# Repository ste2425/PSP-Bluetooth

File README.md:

# PSP-Bluetooth

--- 

ℹ️ **Name Change**  This project was formerly called the `PSP-Consolizer`. The project has since been renamed to `PSP-Bluetooth` as the term `Consolizer` usually makes people think of video output which this project never worked with. 

If you wish to see the legacy `PSP-Consolizer` project it is accessible on the `legacy` branch [here](https://github.com/ste2425/PSP-Bluetooth/tree/legacy)

---

This project aims to add Bluetooth controller support to the PSP 1k, 2k and 3k models using an ESP32.

---

It aims to solve to problems:

- [x] Using the PSP as a consolizer
- [ ] Using the PSP as a dockable console (like the Nintendo Switch)

## Progress so far
* Fully functional hardware that replaces the UMD drive
* Partially functional hardware for portable version
* Fully functional consolizer implementation that works for both the 2K and 3K consoles
* Fully functional firmware that offer configurable controller mappings and OTA updates
* Single click programming via a Web app for Serial and OTA programming. No extra tools needed, it downloads the binaries and does everything
* Partially functional controller mappings via the web app.

## Web app

The web app can be found here [PSP-Bluetooth](https://ste2425.github.io/PSP-Bluetooth/).

## Repository Structure

### /software

This contains the firmware for the ESP32. It is built using the Arduino core and maanaged via the Arduino CLI. To build it the cli needs to be installed with the command `arduino-cli` globally available. 

See [it's readme](./software/Readme.md) for more info.

### /installer

This contains the software for the Web app. It as an Angular application built using Angular Material and deployed to GitHub pages via GitHub Actions.

See [it's readme](./installer/README.md) for more info.

### /Hardware

This contians all the hardware files for custom FPC's and the mod board itself.

See [it's readme](./hardware/Readme.md) for more info.

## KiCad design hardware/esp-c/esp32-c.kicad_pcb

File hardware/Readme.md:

# Hardware

This is the source for the Kicad project for the PSP Bluetooth hardware.

# Parts

I use JLCPCB for my assembly and as such the parts used are sourced from their catalog.

## Adding a part

See [Changing Parts](./ChangingParts.md) for more info.

## Generating JLCPCB production files

See [Generating Gerbers](./GenerateGerbers.md) for more info.

# Projects

# Analog

FPC for the analog stick intercept for 2K PSP's. This allows us to inject analog stick values without soldering to the console.

# Buttons Super

FPC for all the buttons intercepts for 2k PSP's combined into a single project. Fabs usually charge extra for all being combined into one.

# Center Buttons

FPC for the center buttons intercept for 2K PSP'script

# ESP

Project for the Mod Board which supports both portable and consolizer

# ESP-C

Project for the Mod Board which only support consolizers. The analog multiplexer for the analog sticks are missing here.

# Right

FPC for just the right buttons for 2K PSP's

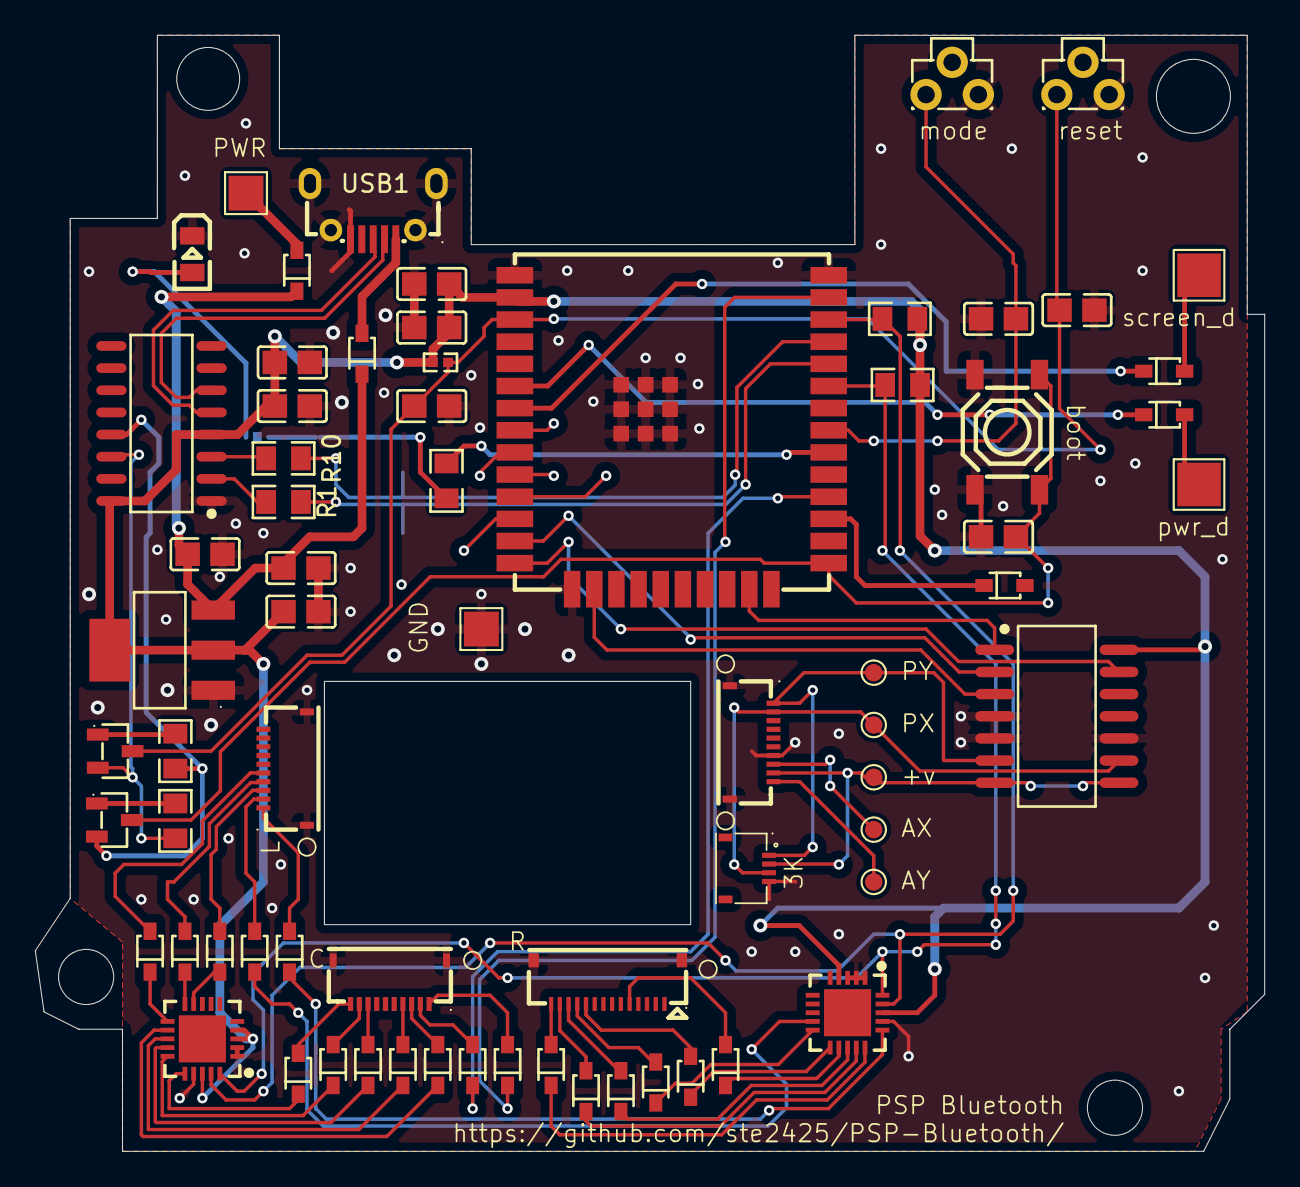
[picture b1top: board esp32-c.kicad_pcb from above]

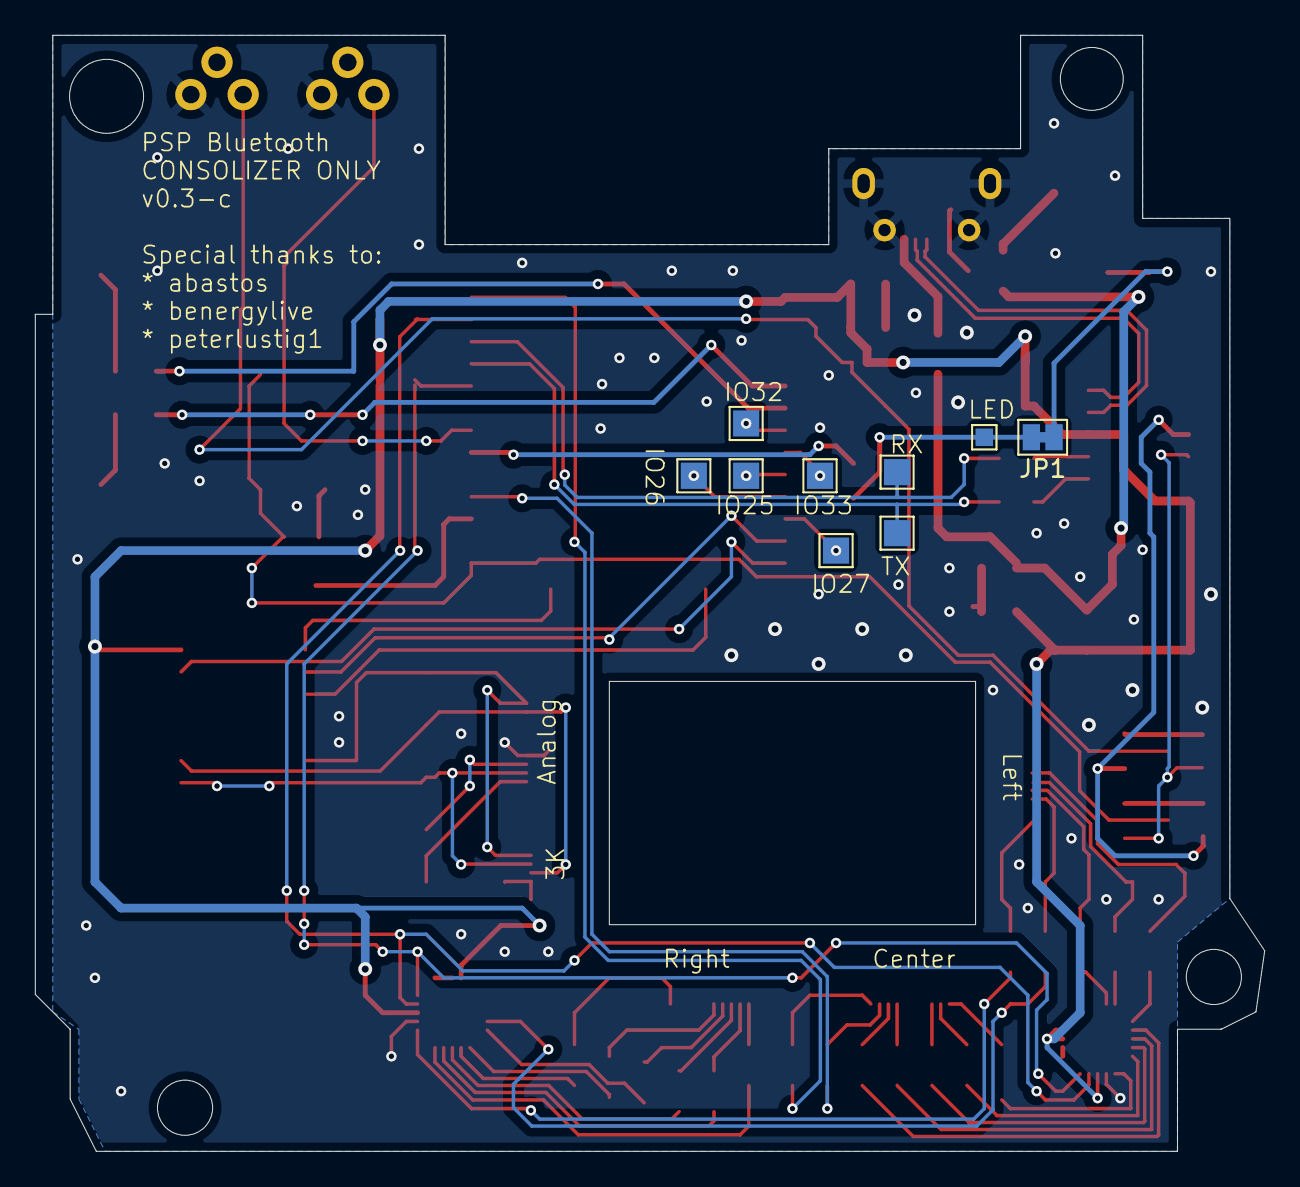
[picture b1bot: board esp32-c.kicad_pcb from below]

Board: 2 copper layers, 70.5 x 64.0 mm, 78 parts (9 on the bottom side), 78 nets.

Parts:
BOOT1: TS-1187A-B-A-B; SW-SMD_4P-L5.1-W5.1-P3.70-LS6.5-TL-2
C1, C11: CL21A226MAQNNNE; C0805
C2, C4, C8, C10, C12: CC0805KRX7R9BB104; C0805
C5: CL21B105KBFNNNE; C0805
C6, C9, C13: CL21A106KAYNNNE; C0805
D1, D2, D3, D4, D5, D6, D7, D8, D9, D10, D11, D12, D13, D20, D21, D22, D23, D24, D25, D26, D27, D28, D29: 1N5819WS; SOD-323_L1.8-W1.3-LS2.5-RD
JP1: SolderJumper_2_Bridged; SolderJumper-2_P1.3mm_Bridged_Pad1.0x1.5mm
LED1: FC-2012HRK-620D; LED0805-R-RD
R1, R10: 0805W8F1001T5E; R0805
R2, R3: 0805W8F1002T5E; R0805
R4, R5: 0805W8F4701T5E; R0805
R7: 0402WGF1002TCE; R0402
R9: 0805W8F3301T5E; R0805
TP1, TP2, TP3, TP7, TP8: TestPoint; TestPoint_Pad_D1.0mm
TP4, TP17: TestPoint; TestPoint_Pad_2.0x2.0mm
TP5, TP6: TestPoint; TestPoint_Pad_2.5x2.5mm
TP9: TestPoint; TestPoint_Pad_1.0x1.0mm
TP12, TP13, TP14, TP15, TP16, TP35, TP36: TestPoint; TestPoint_Pad_1.5x1.5mm
U1, U4: MCP23008-E/ML; QFN-20_L4.0-W4.0-P0.50-BL-EP2.7
U2: CH340C_C7464026; SOP-16_L10.0-W3.9-P1.27-LS6.0-BL
U3, U8: SS8050_C2150; SOT-23-3_L2.9-W1.3-P1.90-LS2.4-BR
U5: MCP42010T-I/SL; SOIC-14_L10.0-W5.5-P1.27-LS7.8-BL
U6, U10, U11: HC-FPC-05-09-10RLTAG; FPC-SMD_10P-P0.50_HC-FPC-05-09-10RLTAG
U7: IPFP051A30472R5; FPC-SMD_4P-P0.50_C9900013912
U9: AMS1117-3_3; SOT-223-3_L6.5-W3.4-P2.30-LS7.0-BR
U12: ESP32-WROOM-32E(4MB); WIFI-SMD_ESP32-WROOM-32E
U13: AFC42-S14FMA-1H; CONN-SMD_14P-P0.50_L3.1-W9.0
U14, U15: TC1109DE26048; SW-TH_3P-L4.5-W4.5-P1.8-LS3.0
USB1: MICROXNJ; MICRO-USB-SMD_MICROXNJ

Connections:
+3.3V: C5.2, C6.2, C8.2, C11.2, C12.2, R4.2, R5.2, R7.2, U1.4 (RESET), U1.18 (VDD), U2.4 (V3), U2.16 (VCC), U4.3 (A0), U4.4 (RESET), U4.18 (VDD), U5.14 (VDD), U9.2 (VOUT), U9.4 (VOUT), U12.2 (3V3)
+5V: D2.2 (A), TP17.1
/ESP32/ESPPowerDetect: D21.1 (K), U12.6 (IO34)
/ESP32/ESPScreenDetect: D22.1 (K), U12.7 (IO35)
/ESP32/ESP_BOOT: BOOT1.3 (C), BOOT1.4 (D), C10.2, U8.3 (C), U12.25 (IO0)
/ESP32/ESP_EN: C4.2, C13.2, R7.1, U3.3 (C), U12.3 (EN), U15.2
/ESP32/ESP_MODE: C2.2, U12.31 (IO19), U14.2
/ESP32/LEDIndicator: R9.2, U12.30 (IO18)
/PSP Pins 2K/+V: TP3.1, U5.7 (PA1), U5.8 (PA0), U7.2, U11.9
/PSP Pins 2K/Analog_x: TP7.1, U11.8
/PSP Pins 2K/Annalog_y: TP8.1, U11.10
/PSP Pins 2K/PSP_x: TP2.1, U5.9 (PW0), U7.3, U11.2
/PSP Pins 2K/PSP_y: TP1.1, U5.6 (PW1), U7.1, U11.1
/USB Serial & Power/USBD+: U2.5 (UD+), USB1.3 (D+)
/USB Serial & Power/USBD-: U2.6 (UD-), USB1.2 (D-)
DTR_PROG: R2.1, U2.13 (DTR#), U8.2 (E)
ESP_I2C_SCL: R5.1, U1.19 (SCL), U4.19 (SCL), U12.36 (IO22)
ESP_I2C_SDA: R4.1, U1.20 (SDA), U4.20 (SDA), U12.33 (IO21)
ESP_SPI_CS: U5.1 (CS#), U12.23 (IO15)
ESP_SPI_MISO: U5.13 (SO), U12.14 (IO12)
ESP_SPI_MOSI: U5.3 (SI), U12.16 (IO13)
ESP_SPI_SCLK: U5.2 (SCK), U12.13 (IO14)
GND: BOOT1.1 (A), BOOT1.2 (B), C1.1, C2.1, C4.1, C5.1, C6.1, C8.1, C9.1, C10.1, C11.1, C12.1, C13.1, LED1.2 (-), TP4.1, U1.1 (A2), U1.2 (A1), U1.3 (A0), U1.17 (VSS), U2.1 (GND), U4.1 (A2), U4.2 (A1), U4.17 (VSS), U5.4 (VSS), U5.5 (PB1), U5.10 (PB0), U6.11, U6.12, U7.4, U9.1 (GND), U10.11, U10.12, U11.7, U11.11, U11.12, U12.1 (GND), U12.15 (GND), U12.38 (GND), U12.39 (GND), U13.0, U14.1, U15.1, USB1.5 (GND), USB1.6 (SH1), USB1.7 (SH2), USB1.8 (SH3), USB1.9 (SH4)
GPIO_GND: D13.1 (K), U12.27 (IO16)
L1: D24.1 (K), U1.16 (GP7)
unnamed: D1.2 (A), U10.1
unnamed: C1.2, C9.2, D2.1 (K), D23.1 (K), U9.3 (VIN)
unnamed: D3.2 (A), U6.2
unnamed: D4.2 (A), U6.3
unnamed: D5.2 (A), U6.4
unnamed: D6.2 (A), U6.5
unnamed: D7.2 (A), U13.14
unnamed: D8.2 (A), U13.13
unnamed: D9.2 (A), U13.12
unnamed: D10.2 (A), U13.11
unnamed: D11.2 (A), U13.10
unnamed: D12.2 (A), U13.5
unnamed: D20.2 (A), U10.2
unnamed: D21.2 (A), TP5.1
unnamed: D22.2 (A), TP6.1
unnamed: D24.2 (A), U6.1
unnamed: D25.2 (A), U10.3
unnamed: D26.2 (A), U10.4
unnamed: D27.2 (A), U10.8
unnamed: D28.2 (A), U10.9
unnamed: D29.2 (A), U10.10
unnamed: JP1.1 (A), LED1.1 (+)
unnamed: JP1.2 (B), R9.1, TP9.1
unnamed: R10.2, U2.3 (RXD)
unnamed: R1.2, U2.2 (TXD)
unnamed: R2.2, U3.1 (B)
unnamed: R3.2, U8.1 (B)
unnamed: TP14.1, U12.10 (IO25)
unnamed: TP13.1, U12.11 (IO26)
unnamed: TP12.1, U12.12 (IO27)
unnamed: TP16.1, U12.8 (IO32)
unnamed: TP15.1, U12.9 (IO33)
PSP_SELECT: D20.1 (K), U12.28 (IO17)
PSP_START: D1.1 (K), U12.37 (IO23)
RTS_PROG: R3.1, U2.14 (RTS#), U3.2 (E)
UART_RX: R10.1, TP36.1, U12.35 (TXD0)
UART_TX: R1.1, TP35.1, U12.34 (RXD0)
VBUS: D23.2 (A), USB1.1 (VBUS)
circle: D10.1 (K), U1.10 (GP1)
cross: D11.1 (K), U1.11 (GP2)
display: D26.1 (K), U4.13 (GP4)
down: D6.1 (K), U4.11 (GP2)
home: D29.1 (K), U4.16 (GP7)
left: D5.1 (K), U4.10 (GP1)
power: D12.1 (K), U1.12 (GP3)
r1: D8.1 (K), U1.14 (GP5)
right: D3.1 (K), U1.9 (GP0)
sound: D25.1 (K), U4.12 (GP3)
square: D7.1 (K), U1.15 (GP6)
triangle: D9.1 (K), U1.13 (GP4)
up: D4.1 (K), U4.9 (GP0)
voldown: D28.1 (K), U4.15 (GP6)
volup: D27.1 (K), U4.14 (GP5)

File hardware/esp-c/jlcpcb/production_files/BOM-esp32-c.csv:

Comment,Designator,Footprint,LCSC
MCP23008-E/ML,"U1,U4",QFN-20_L4.0-W4.0-P0.50-BL-EP2.7,C144211
CL21A106KAYNNNE,"C13,C6,C9",C0805,C15850
0805W8F1002T5E,"R2,R3",R0805,C17414
0805W8F1001T5E,"R1,R10",R0805,C17513
0805W8F4701T5E,"R4,R5",R0805,C17673
1N5819WS,"D1,D10,D11,D12,D13,D2,D20,D21,D22,D23,D24,D25,D26,D27,D28,D29,D3,D4,D5,D6,D7,D8,D9",SOD-323_L1.8-W1.3-LS2.5-RD,C191023
SS8050_C2150,"U3,U8",SOT-23-3_L2.9-W1.3-P1.90-LS2.4-BR,C2150
TC1109DE26048,"U14,U15",SW-TH_3P-L4.5-W4.5-P1.8-LS3.0,C22459542
0402WGF1002TCE,R7,R0402,C25744
0805W8F3301T5E,R9,R0805,C26010
CL21B105KBFNNNE,C5,C0805,C28323
TS-1187A-B-A-B,BOOT1,SW-SMD_4P-L5.1-W5.1-P3.70-LS6.5-TL-2,C318884
MICROXNJ,USB1,MICRO-USB-SMD_MICROXNJ,C404969
CL21A226MAQNNNE,"C1,C11",C0805,C45783
AFC42-S14FMA-1H,U13,CONN-SMD_14P-P0.50_L3.1-W9.0,C466533
CC0805KRX7R9BB104,"C10,C12,C2,C4,C8",C0805,C49678
IPFP051A30472R5,U7,FPC-SMD_4P-P0.50_C9900013912,C5127055
HC-FPC-05-09-10RLTAG,"U10,U11,U6",FPC-SMD_10P-P0.50_HC-FPC-05-09-10RLTAG,C5213750
MCP42010T-I/SL,U5,SOIC-14_L10.0-W5.5-P1.27-LS7.8-BL,C54781
AMS1117-3_3,U9,SOT-223-3_L6.5-W3.4-P2.30-LS7.0-BR,C6186
ESP32-WROOM-32E(4MB),U12,WIFI-SMD_ESP32-WROOM-32E,C701341
CH340C_C7464026,U2,SOP-16_L10.0-W3.9-P1.27-LS6.0-BL,C7464026
FC-2012HRK-620D,LED1,LED0805-R-RD,C84256

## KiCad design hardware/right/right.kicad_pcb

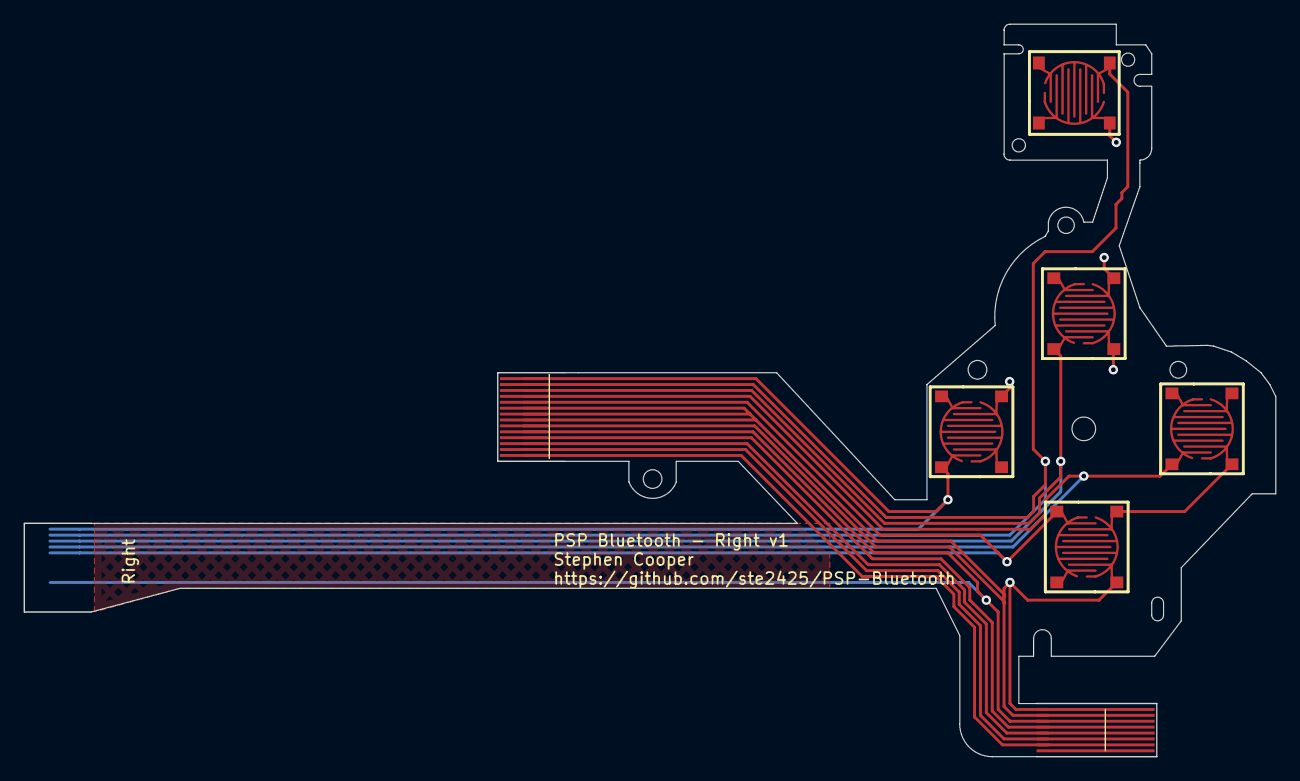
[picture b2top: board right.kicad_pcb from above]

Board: 2 copper layers, 105.9 x 62.0 mm, 8 parts (1 on the bottom side), 11 nets.

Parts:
C1, C4: flex-conector_14; flex_long_14
C3: flex-conector_8_1; flex_long_8
L2, L3, L4, L5, L6: SKRRABE010; KEY-SMD_4P-L5.2-W5.2-P3.70-LS6.4_1

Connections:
/Circle: C1.4, C4.11, L6.1
/LED +5v: C3.7, C4.1
/R1: C1.2, C4.13, L3.1
/Square: C1.1, C4.14, L5.1
/Triangle: C1.3, C4.12, L4.1
/chargeLED: C3.6, C4.2
/cross: C1.5, C4.10, L2.1
/gnd: C3.1, C3.2, C4.6, C4.7, C4.8, C4.9, L2.2, L3.2, L4.2, L5.2, L6.2
/keyHold: C3.4, C4.4
/keyPower: C1.10, C3.3, C4.5
/powerLED: C3.5, C4.3

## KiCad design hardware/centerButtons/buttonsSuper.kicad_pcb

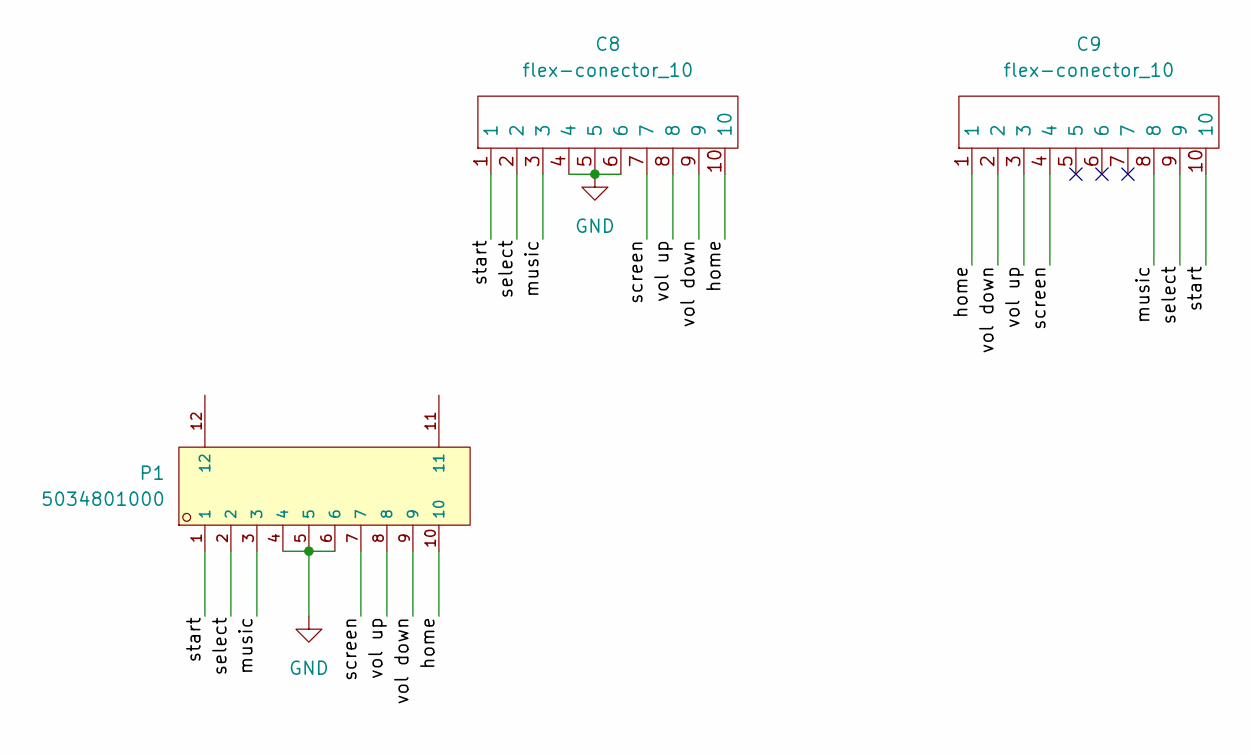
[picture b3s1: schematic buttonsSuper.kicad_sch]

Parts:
C8, C9: flex-conector_10; flex_short_10
P1: 5034801000; FPC-SMD_5034801000; LCSC C127355

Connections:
/home: C8.10, C9.1, P1.10
/music: C8.3, C9.8, P1.3
/screen: C8.7, C9.4, P1.7
/select: C8.2, C9.9, P1.2
/start: C8.1, C9.10, P1.1
/vol down: C8.9, C9.2, P1.9
/vol up: C8.8, C9.3, P1.8
GND: C8.4, C8.5, C8.6, P1.4, P1.5, P1.6

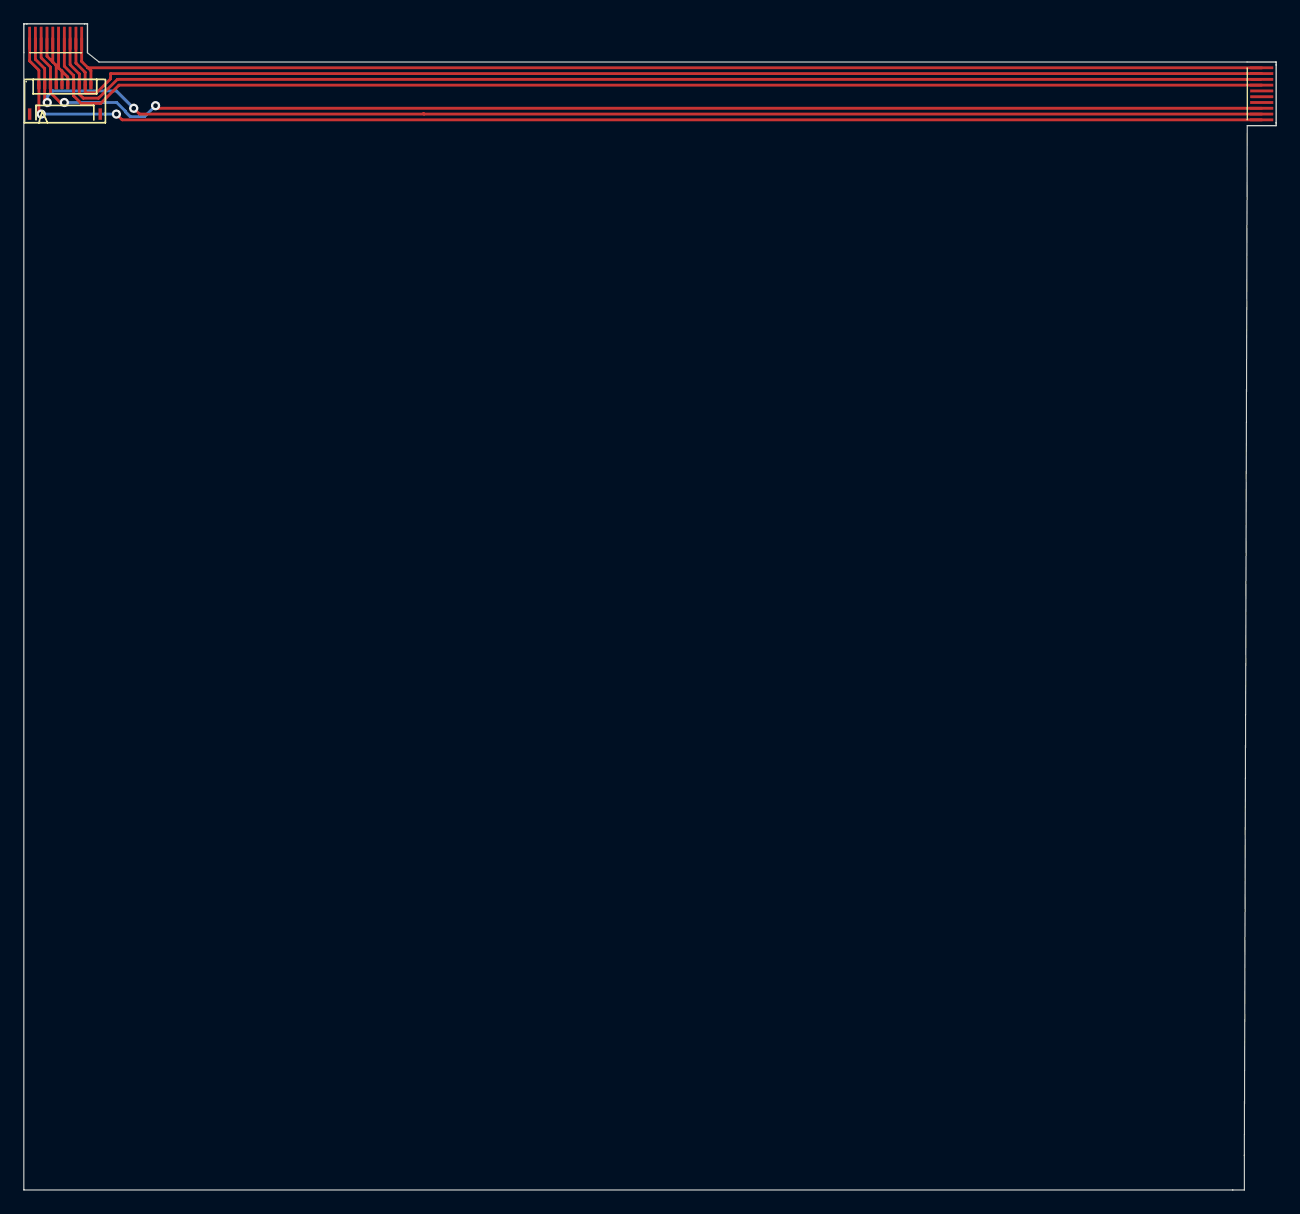
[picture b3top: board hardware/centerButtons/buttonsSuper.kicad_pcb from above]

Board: 2 copper layers, 108.2 x 100.8 mm, 3 parts (0 on the bottom side), 8 nets.

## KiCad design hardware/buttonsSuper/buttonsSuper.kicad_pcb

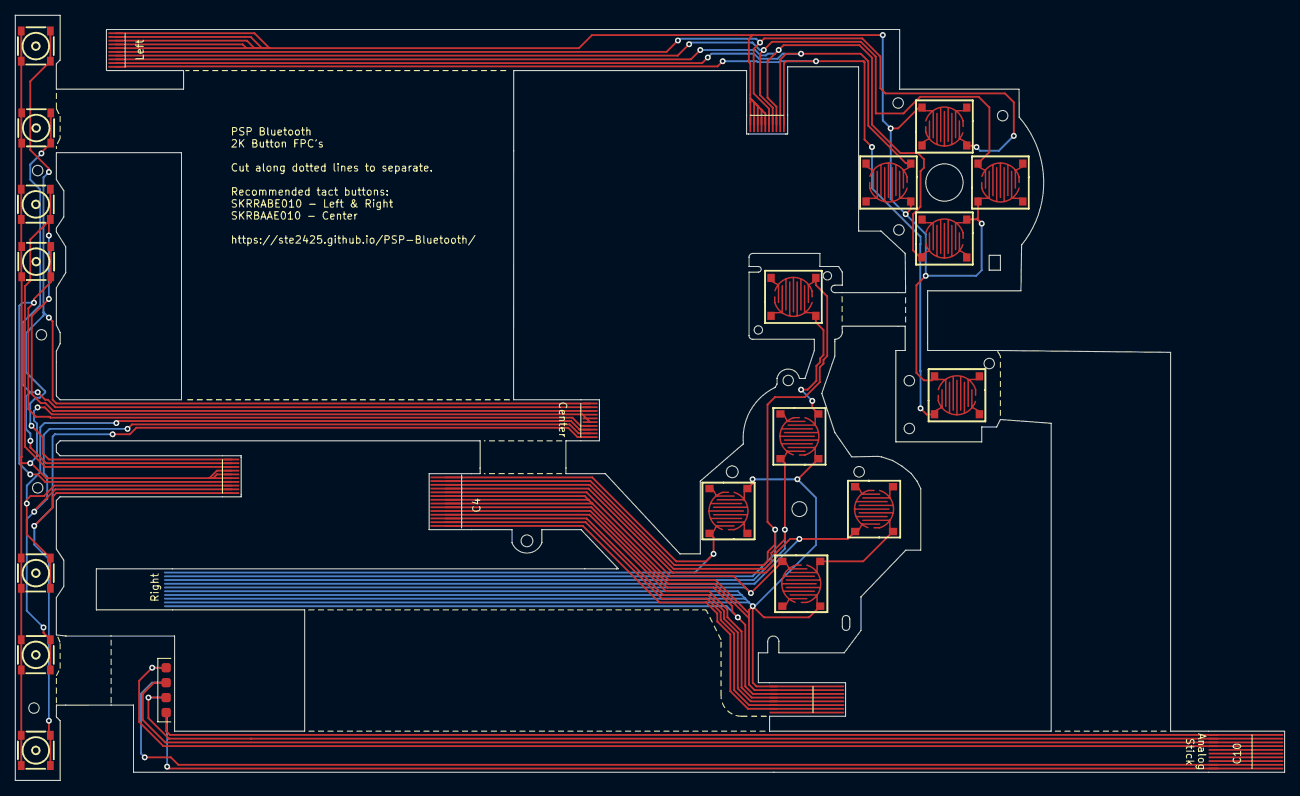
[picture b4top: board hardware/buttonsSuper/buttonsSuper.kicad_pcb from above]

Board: 2 copper layers, 170.0 x 102.5 mm, 26 parts (1 on the bottom side), 31 nets.

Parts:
C1, C2, C8, C9: flex-conector_10; flex_short_10
C3: flex-conector_8_1; flex_long_8
C4: flex-conector_14; flex_long_14
C5, C10: flex-conector_10; flex_long_10
C6: PSP-analog
DOWN1: SKRRABE010; KEY-SMD_4P-L5.2-W5.2-P3.70-LS6.4_1
L1, L2, L3, L4, L5, L6: SKRRABE010; KEY-SMD_4P-L5.2-W5.2-P3.70-LS6.4_1
LEFT1: SKRRABE010; KEY-SMD_4P-L5.2-W5.2-P3.70-LS6.4_1
RIGHT1: SKRRABE010; KEY-SMD_4P-L5.2-W5.2-P3.70-LS6.4_1
U1, U2, U3, U4, U5, U6, U7: SKRBAAE010; KEY-SMD_4P-L4.8-W4.8-P3.65_SKRBAAE010
UP1: SKRRABE010; KEY-SMD_4P-L5.2-W5.2-P3.70-LS6.4_1

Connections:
/+v: C6.3 (Analog_+v), C6.7 (PSP_+v), C10.2 (+v)
/Analog_y: C6.4 (Analog_y), C10.1 (Analog_y)
/Circle: C4.11, C5.4, L6.1
/LED +5v: C3.7, C4.1
/PSP_x: C6.6 (PSP_x), C10.9 (PSP_x)
/PSP_y: C6.8 (PSP_y), C10.10 (PSP_y)
/R1: C4.13, C5.2, L3.1
/Square: C4.14, C5.1, L5.1
/Triangle: C4.12, C5.3, L4.1
/analog_x: C6.2 (Analog_x), C10.3 (Analog_X)
/chargeLED: C3.6, C4.2
/cross: C4.10, C5.5, L2.1
/down: C1.5, C2.5, DOWN1.1
/gnd: C3.1, C3.2, C4.6, C4.7, C4.8, C4.9, C5.6, C5.7, C5.8, C5.9, L2.2, L3.2, L4.2, L5.2, L6.2
/gnd2: C8.4, C8.5, C8.6, C9.4, C9.5, C9.6, U1.1, U1.3, U2.1, U2.3, U3.1, U3.3, U4.1, U4.3, U5.1, U5.3, U6.1, U6.3, U7.1, U7.3
/gnd3: C6.1 (Analog_gnd), C6.5 (PSP_gnd), C10.4 (gnd)
/home: C8.10, C9.10, U7.2, U7.4
/keyHold: C3.4, C4.4
/keyPower: C3.3, C4.5, C5.10
/l1: C1.1, C2.1, L1.1
/left: C1.4, C2.4, LEFT1.1
/music: C8.3, C9.3, U1.2, U1.4
/powerLED: C3.5, C4.3
/right: C1.2, C2.2, RIGHT1.1
/screen: C8.7, C9.7, U2.2, U2.4
/select: C8.2, C9.2, U4.2, U4.4
/start: C8.1, C9.1, U3.2, U3.4
/up: C1.3, C2.3, UP1.1
/vol down: C8.9, C9.9, U6.2, U6.4
/vol up: C8.8, C9.8, U5.2, U5.4
GND: C1.6, C1.7, C1.8, C1.9, C1.10, C2.6, C2.7, C2.8, C2.9, C2.10, DOWN1.2, L1.2, LEFT1.2, RIGHT1.2, UP1.2

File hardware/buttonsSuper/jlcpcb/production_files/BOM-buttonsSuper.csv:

Comment,Designator,Footprint,LCSC
5034801000,P1,FPC-SMD_5034801000,C127355
K2-1187SQ-E4SW-06,"CIRCLE1,CROSS1,DOWN1,L1,LEFT1,R1,RIGHT1,SQUARE1,TRIANGLE1,UP1",KEY-SMD_4P-L5.2-W5.2-P3.70-LS6.4_1,C477942
PSP-analog,C6,PSP-analog,
flex-conector_14,C4,flex_long_14,
flex-conector_8_1,C3,flex_long_8,
flex-conector_10,C7,flex_long_10,
flex-conector_10,C1,flex_short_10,
flex-conector_10,C2,flex_short_10,
flex-conector_10,C5,flex_long_10,
flex-conector_10,C8,flex_short_10,

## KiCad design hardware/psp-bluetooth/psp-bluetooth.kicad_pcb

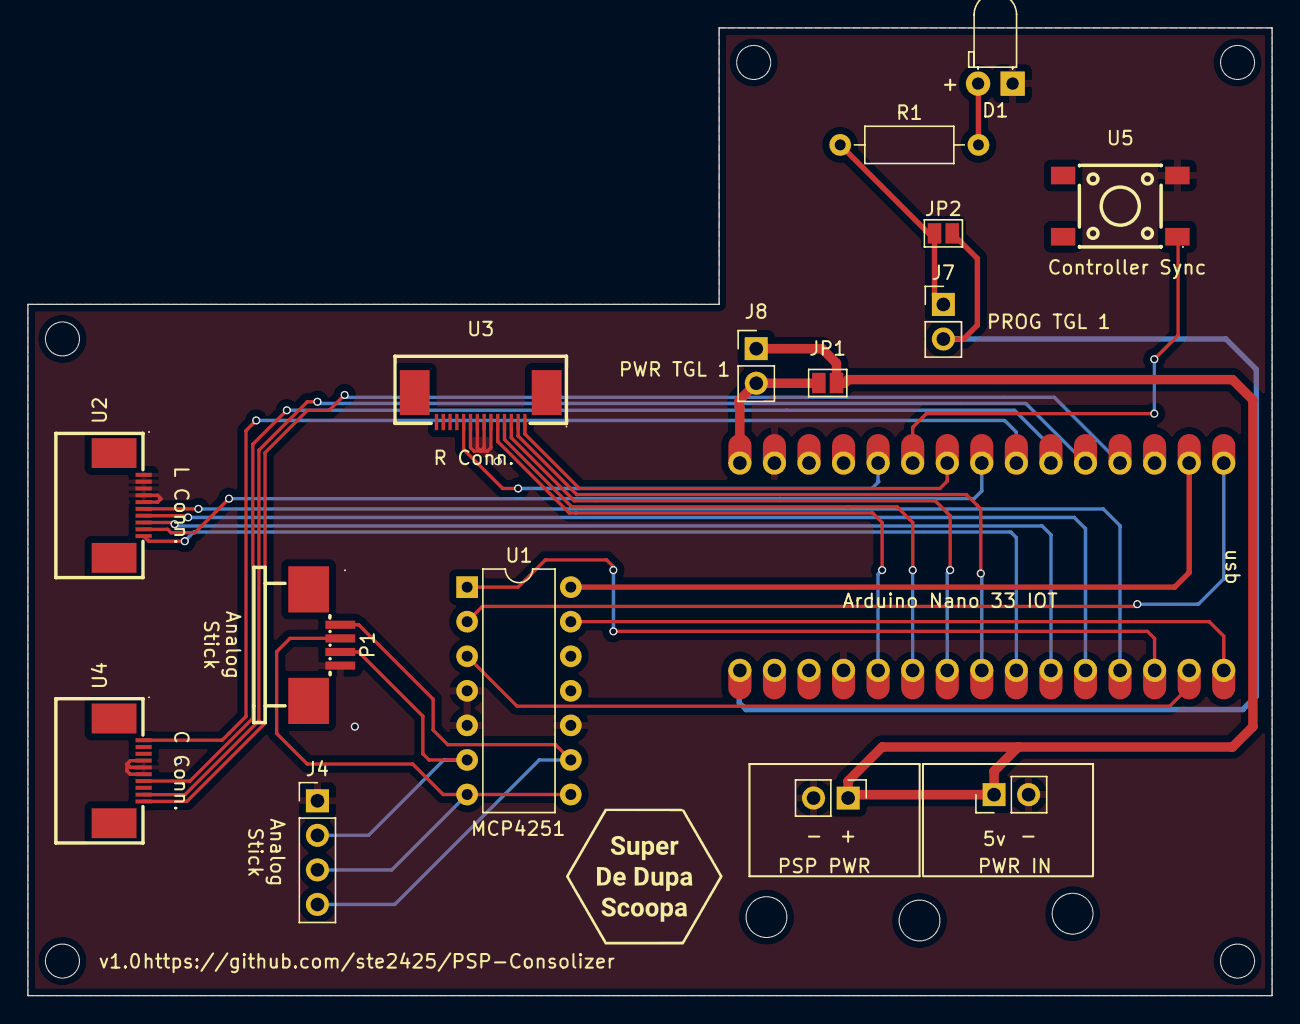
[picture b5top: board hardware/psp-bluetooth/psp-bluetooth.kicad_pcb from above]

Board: 2 copper layers, 91.4 x 71.1 mm, 21 parts (0 on the bottom side), 30 nets.

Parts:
D1: LED; LED_D3.0mm_Horizontal_O1.27mm_Z6.0mm
H1, H2, H3, H4, H5: MountingHole; MountingHole_2.5mm
J1: Arduino-NANO-33; NANO_33_Socket_Castell&SMD
J2, J3: Conn_01x02; PinHeader_1x02_P2.54mm_Vertical
J4: Analog Connector; PinHeader_1x04_P2.54mm_Vertical
J7: Programming Header 1; PinHeader_1x02_P2.54mm_Vertical
J8: Vin Toggle; PinHeader_1x02_P2.54mm_Vertical
JP1: SJ Vin Toggle; SolderJumper-2_P1.3mm_Open_Pad1.0x1.5mm
JP2: SJ LED Indicator; SolderJumper-2_P1.3mm_Open_Pad1.0x1.5mm
P1: FPC_4P_Pull_type_1_0MM_Under_the_next; FPC-SMD_AFA07-S04FCC-00
R1: 140 ohm; R_Axial_DIN0207_L6.3mm_D2.5mm_P10.16mm_Horizontal
U1: MCP4251-xxxx-P; DIP-14_W7.62mm
U2, U4: AFC07-S10ECA-00; FPC-SMD_P0.50-10P_LCS-SJ-H2.0
U3: AFC07-S14ECA-00; FPC-SMD_P0.50-14P_LCS-SJ-H2.0
U5: TS-1102SD-A-F-R; SW-SMD_4P-L6.0-W6.0-P4.50-LS9.2

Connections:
+3V3: J1.2 (+3.3v), U1.14 (VDD)
/1(Tx): J1.16 (TX), J7.2, JP2.2 (B)
/2: J1.20 (D2~), U3.5
/3(**): J1.21 (D3~), U3.4
/4: J1.22 (D4), U3.3
/5(**): J1.23 (D5~), U3.2
/6(**): J1.24 (D6~), U2.10
/7: J1.25 (D7), U2.8
/8: J1.26 (D8), U2.7
/9(**): J1.27 (D9~), U2.6
/10(**/SS): J1.28 (D10~), U1.1 (~CS)
/11(**/MOSI): J1.29 (D11~), U1.3 (SDI)
/12(MISO): J1.30 (D12~), U1.13 (SDO)
/13(SCK): J1.1 (D13), U1.2 (SCK)
/A0 (D14): J1.4 (D14), U4.10
/A1 (D15): J1.5 (D15), U4.9
/A2 (D16): J1.6 (D16~), U4.7
/A3 (D17): J1.7 (D17~), U4.1
/A4 (D18): J1.8 (D18), U2.9
/A5 (D19): J1.9 (D19~), U3.1
/A6 (D20): J1.10 (D20), U5.1
/A7 (D21): J1.11 (D21), U3.10
/P0A/P1A: J4.3, P1.3, U1.7 (P1A), U1.8 (P0A)
/P0W: J4.4, P1.4, U1.9 (P0W)
/P1W: J4.2, P1.2, U1.6 (P1W)
GND: D1.1 (K), J1.14 (GND), J1.19 (GND), J2.2, J3.2, J4.1, P1.1, U1.4 (VSS), U1.5 (P1B), U1.10 (P0B), U2.1, U2.2, U2.3, U2.4, U2.5, U3.6, U3.7, U3.8, U3.9, U4.4, U4.5, U4.6, U5.3
unnamed: D1.2 (A), R1.2
unnamed: J7.1, JP2.1 (A), R1.1
unnamed: J2.1, J3.1, J8.1, JP1.1 (A)
VIN: J1.15 (VIN), J8.2, JP1.2 (B)

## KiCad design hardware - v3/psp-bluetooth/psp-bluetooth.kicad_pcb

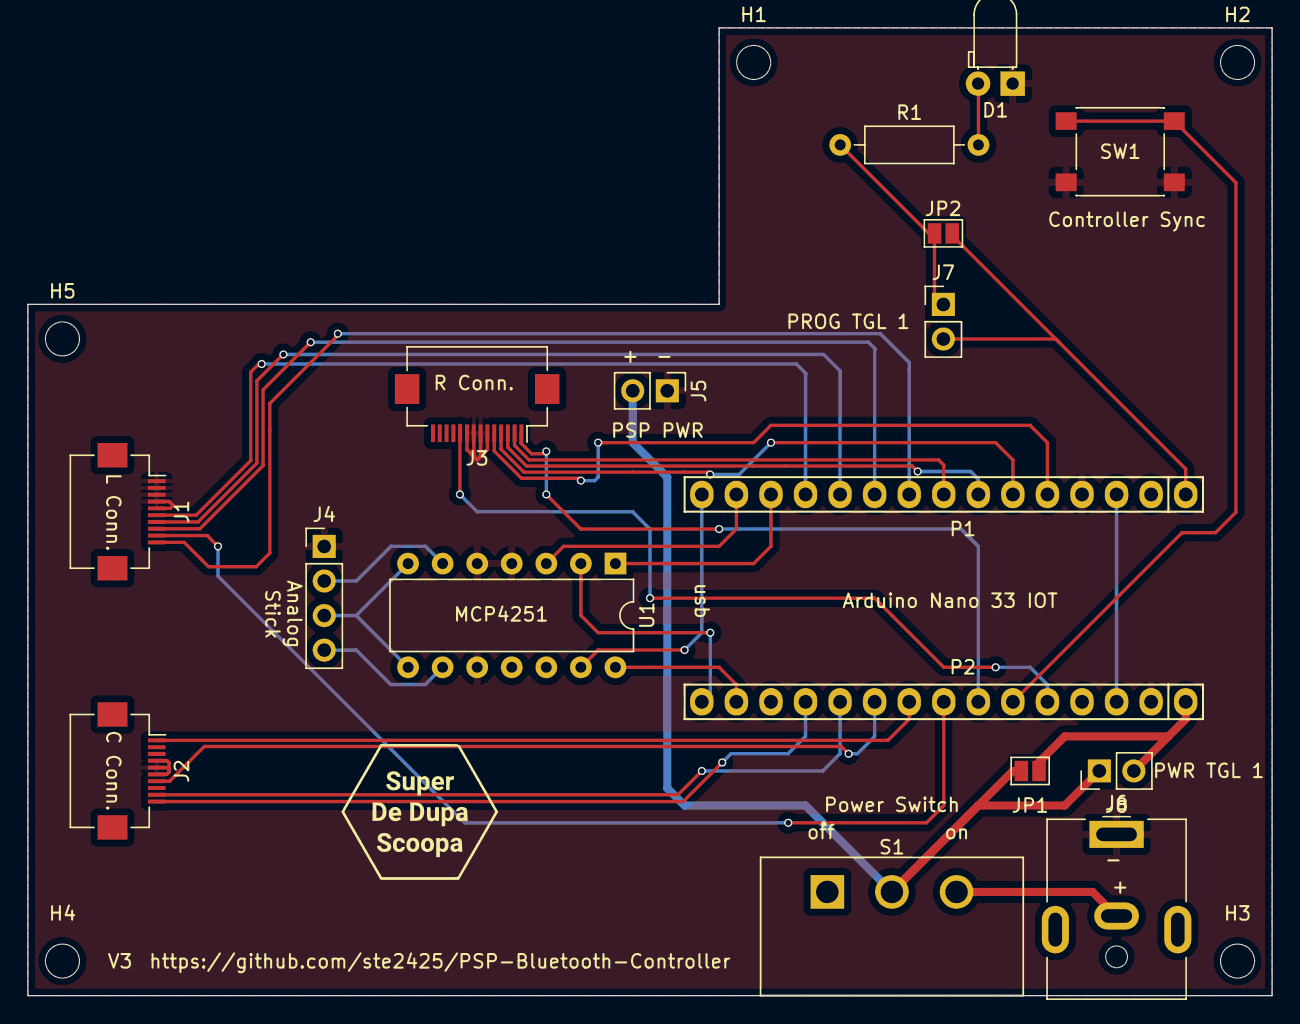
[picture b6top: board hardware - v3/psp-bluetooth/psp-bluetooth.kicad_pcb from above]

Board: 2 copper layers, 91.4 x 71.1 mm, 22 parts (0 on the bottom side), 32 nets.

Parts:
D1: LED; LED_D3.0mm_Horizontal_O1.27mm_Z6.0mm
H1, H2, H3, H4, H5: MountingHole; MountingHole_2.5mm
J1: Left Connector; Hirose_FH12-10S-0.5SH_1x10-1MP_P0.50mm_Horizontal
J2: Center Connector; Hirose_FH12-10S-0.5SH_1x10-1MP_P0.50mm_Horizontal
J3: Right Connector; Hirose_FH12-14S-0.5SH_1x14-1MP_P0.50mm_Horizontal
J4: Analog Connector; PinHeader_1x04_P2.54mm_Vertical
J5: PSP Power out; PinHeader_1x02_P2.54mm_Vertical
J6: Barrel_Jack; BarrelJack_CUI_PJ-063AH_Horizontal
J7: Programming Header 1; PinHeader_1x02_P2.54mm_Vertical
J8: Vin Toggle; PinHeader_1x02_P2.54mm_Vertical
JP1: SJ Vin Toggle; SolderJumper-2_P1.3mm_Open_Pad1.0x1.5mm
JP2: SJ LED Indicator; SolderJumper-2_P1.3mm_Open_Pad1.0x1.5mm
P1: Digital; Socket_Strip_Arduino_1x15
P2: Analog; Socket_Strip_Arduino_1x15
R1: 140 ohm; R_Axial_DIN0207_L6.3mm_D2.5mm_P10.16mm_Horizontal
S1: L102021ML04Q; SW_L102021ML04Q
SW1: SW_Push; SW_Push_1P1T_NO_6x6mm_H9.5mm
U1: MCP4251-xxxx-P; DIP-14_W7.62mm

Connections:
+3V3: P2.14, U1.14 (VDD)
/1(Tx): J7.2, JP2.2 (B), P1.1
/2: J3.5, P1.5
/3(**): J3.4, P1.6
/4: J3.3, P1.7
/5(**): J3.2, P1.8
/6(**): J1.10, P1.9
/7: J1.8, P1.10
/8: J1.7, P1.11
/9(**): J1.6, P1.12
/10(**/SS): P1.13, U1.1 (~CS)
/11(**/MOSI): P1.14, U1.3 (SDI)
/12(MISO): P1.15, U1.13 (SDO)
/13(SCK): P2.15, U1.2 (SCK)
/A0 (D14): J2.10, P2.12
/A1 (D15): J2.9, P2.11
/A2 (D16): J2.7, P2.10
/A3 (D17): J2.1, P2.9
/A4 (D18): J1.9, P2.8
/A5 (D19): J3.1, P2.7
/A6 (D20): P2.6, SW1.1
/A7 (D21): J3.10, P2.5
/P0A/P1A: J4.3, U1.7 (P1A), U1.8 (P0A)
/P0W: J4.4, U1.9 (P0W)
/P1W: J4.2, U1.6 (P1W)
/Reset: P1.3, P2.3
GND: D1.1 (K), J1.1, J1.2, J1.3, J1.4, J1.5, J2.4, J2.5, J2.6, J3.6, J3.7, J3.8, J3.9, J4.1, J5.1, J6.1, P1.4, P2.2, SW1.2, U1.4 (VSS), U1.5 (P1B), U1.10 (P0B)
unnamed: D1.2 (A), R1.2
unnamed: J5.2, J8.1, JP1.1 (A), S1.2
unnamed: J6.2, S1.3
unnamed: J7.1, JP2.1 (A), R1.1
VIN: J8.2, JP1.2 (B), P2.1

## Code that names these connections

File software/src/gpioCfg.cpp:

#include "gpioCfg.h"

static Preferences preferences;

// Note not all ESP GPIO is safe to use, some pins have specific uses
// Others output a PWM signal on boot. These pins could be used with extra hardware
// to protect the PSP however, but for now they are avoided.
uint8_t defaultGPIO[15] = {
    4, //dpadup
    18, //dpaddown
    16, //dpadleft
    17, //dpadright
    13, //cross
    19, //triangle
    21, //square
    22, //circle
    23, //l1
    25, //r1
    26, //start
    27, //select
    32, //home
    33, //screen
    34 //Mode Change Btn - INPUT ONLY
};

GPIOPinConfig gpioCfg_getConfig()
{
    preferences.begin(GPIONamespace, false);

    GPIOPinConfig config;

    config.DPadUp = preferences.getChar("dpadup", defaultGPIO[PSPDPadUp]);
    config.DPadDown = preferences.getChar("dpaddown", defaultGPIO[PSPDPadDown]);
    config.DpadLeft = preferences.getChar("dpadleft", defaultGPIO[PSPDPadLeft]);
    config.DpadRight = preferences.getChar("dpadright", defaultGPIO[PSPDPadRight]);
    config.Cross = preferences.getChar("crossbtn", defaultGPIO[PSPCross]);
    config.Triangle = preferences.getChar("trianglebtn", defaultGPIO[PSPTriangle]);
    config.Square = preferences.getChar("squarebtn", defaultGPIO[PSPSquare]);
    config.circle = preferences.getChar("circlebtn", defaultGPIO[PSPCircle]);
    config.L1 = preferences.getChar("l1btn", defaultGPIO[PSPL1]);
    config.R1 = preferences.getChar("r1btn", defaultGPIO[PSPR1]);
    config.Start = preferences.getChar("startbtn", defaultGPIO[PSPStart]);
    config.Select = preferences.getChar("selectbtn", defaultGPIO[PSPSelect]);
    config.Home = preferences.getChar("homebtn", defaultGPIO[PSPHome]);
    config.Screen = preferences.getChar("screenbtn", defaultGPIO[PSPScreen]);
    config.ModeChange = preferences.getChar("modechangebtn", defaultGPIO[BTNModeChange]);

    preferences.end();

    return config;
}

uint8_t gpioCfg_getPin(GPIOTypes type)
{
    preferences.begin(GPIONamespace, false);
    uint8_t value = preferences.getChar((const char*)type, defaultGPIO[type]);
    preferences.end();
    return value;
}

void gpioCfg_setPin(GPIOTypes type, uint8_t value)
{
    preferences.begin(GPIONamespace, false);
    preferences.putChar((const char*)type, value);
    preferences.end();
}

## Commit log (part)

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2022-04-09 Initial implementation
2022-04-09 Fix instant release of button problem
2022-04-13 Final mapping
2022-05-12 Adding system buttons
2022-05-19 Update PSP-Bluetooth-Controller.ino
    wip
2022-05-19 Update PSP-Bluetooth-Controller.ino
    test
2022-05-21 Update PSP-Bluetooth-Controller.ino
    wup
2022-06-01 Update PSP-Bluetooth-Controller.ino
    Added psp analog stick support
2022-06-07 Added hardware V1
2022-06-07 Analog stick (#1)
    Added hardware V1
2022-06-15 Initial work and hardware stuff
2022-06-15 Move around stuff
2022-06-17 Adding mappings for analog sticks
2022-06-23 Added PCB pinout
2022-07-17 Final
2022-07-17 Added Mappings (#2)
    * Initial work and hardware stuff
    * Move around stuff
    * Adding mappings for analogue sticks
    * Added PCB pinout
    * Final
2022-07-24 Added hardware v3
2022-07-24 updated gerbers
2022-08-01 Finished
2022-08-01 Hardware v3 (#3)
    * Added hardware v3
2022-09-26 Made kicad project portable and finished V1.
2022-09-29 Added 3D printable mount, updated docs
2022-09-29 remove stupid ovrlay that dont work on github
2022-09-29 Added boot LED & controller LED support
2022-10-11 Alter warm boot delay
2022-10-14 Added libraries
2022-10-14 test
2022-10-15 copy consolizer bin
2022-10-16 envs
2022-10-16 add release step
2022-10-23 Added controller LED stuff
2022-10-24 Testing release stuff
2022-10-24 this should do it
2022-10-24 testssss
2022-10-24 Update yml
2022-11-03 Add docs
2022-11-03 Update docs
2022-11-04 Updated readme to look every so slightly better. Might as well make an effort i suppose
2022-11-05 Added USer Guide
    Made build guide more explicity on MCP4251
2022-11-13 initial quick shutdown
2022-11-13 Fix build
2022-11-13 Added user guide
2022-11-13 Update bluepad version
2022-11-15 Disabled auto power on && added manual display control
2022-11-16 Added vol up/down
2022-11-17 Added vol up using power
2022-11-20 multi time
    lol
    lol
2022-11-20 lol some stuff
    Do something else
    Be cool
2022-11-20 make it work bro lol
    sdfs
    * lol
    * troll
2022-11-20 Final Test
2022-11-21 Update config (#4)
    Update workspace config to send commit message and sha to the installer.
2022-11-21 Added more documentation
2023-12-14 unknown need to figure out what i was doing
2024-05-31 Clean house
2024-05-31 Initial
2024-06-04 Initial WIP. PSP buttons works. BLE not tested
2024-06-17 Added actions for PSP Bluetoothj
2024-06-17 Name Github action properly
2024-06-17 Change CWD of script!
2024-06-17 This is going to nbe painful
2024-06-17 All the pain
2024-06-17 I need to pull the source down obviously 🤦
2024-06-17 Initial Arduino install script
2024-06-17 Sudo all the thngs
2024-06-17 Test creating release
2024-06-17 Updated github actions to indlude commit message in release
2024-06-19 Added installer app
2024-06-19 More changes
2024-06-19 Apply automatic changes
2024-06-19 Initial test. The web installer *should* be working now
2024-06-19 Super Super Changes
2024-06-22 [web app] Added serial page
2024-07-01 Web app installer done, for now
2024-07-01 Super Duper
2024-07-04 Improve local programmer
2024-07-08 Initial mappings data structure
2024-08-11 Add hardware files
2024-10-09 Added hardware 0.2 - Added right FPC
2024-10-20 stuff
2024-11-07 Initial fully working PSP-Bluetooth.
    **NOTE**
    * This is hard coded for consolizers
    * This does not support OTA
    * This is hard coded to forget paired controllers on power cycle
    * This is very much early alpha release - expect issues
2024-11-08 Initially fully working PSP Bluetooth
    **NOTE**
    * This is hard coded for consolizers
    * This does not support OTA
    * This is hard coded to forget paired controllers on power cycle
    * This is very much early alpha release - expect issues
2024-11-08 Initial PSP Bluetooth
    **NOTE**
    * This is hard coded for consolizers
    * This does not support OTA
    * This is hard coded to forget paired controllers on power cycle
    * This is very much early alpha release - expect issues
2024-11-09 Update installer yaml for more static pages
2024-11-09 Code change to trigger workflows - i need to fix them
2024-11-09 This should add the extra static files. I need to get better at this.
2024-11-09 Add 404 page, will it work first time?
2024-11-09 redirect logic
2024-11-09 maybe nearly
2024-11-14 Enable OTS by default
2024-11-16 Changes:
    * Fix DPAD Right always being pressed for unused button mappings
    * Enable BLE service, hard coded (for web app)
    * Initial OTA and mappings saving implemenation
2024-11-18 * Added correct error responses for OTA commands
2024-11-18 * Fix workflow to facilitate OTA upload
2024-11-18 random code change to force a re-run of CI
2024-11-18 force change
2024-11-18 Just do the OTA
2024-11-18 just do it
2024-11-18 create missing binaries
2024-11-19 * Added ability for CI to inject version number * Added correct OTA abortion logic
2024-11-19 * Added ability to abort OTA should client disconenct
2024-11-19 Added initial OTA web app
2024-11-20 Fixed version number injection - maybe
2024-11-20 change to force build to test versions
2024-11-22 Finished OTA work within web app
2024-11-22 typo
2024-11-23 Hardware changes of some descirption, not sure what
2024-11-23 Added BLE detection and initial config mappings
2024-11-27 Develop (#13)
    * Initial WIP. PSP buttons works. BLE not tested
    * wip
    * wup
    * wip
    * Added actions for PSP Bluetoothj
    * Name Github action properly
2024-11-30 Potentially fully working
    * Added button controls
    * Added status LED
    * Made PSP booting async to not block status LED pattern
2024-11-30 change git workflow to base on tags. Added release notes file.
2024-11-30 more ci changes
2024-11-30 workflow changes
2024-11-30 update web app for production releases
2024-11-30 Modify home page
2024-11-30 final web app changes
2024-12-01 v1.0.0 release notes
2024-12-01 changing homepae heading
2024-12-01 Improved landing page for web app
2024-12-01 Fixed broken home page image
2024-12-01 Added reload mappings command
2024-12-03 Added app settings to web app
2024-12-03 Added cache busting for theme
2024-12-05 Added ability for web app to configure and save mappings - still work to do
2024-12-06 [1.1.0] Added abiloity to reload saved button mappings
2024-12-06 Fixe dpotential issue with corrupted JSON - maybe
2024-12-06 Enabled configuration and fixed analog mapping
2024-12-07 Fix issue with analog stick mappings
2024-12-12 Added configuration tour
2024-12-12 spelling
2025-01-08 [Hardware] Added LED pad and changed switch to right angle
2025-01-09 [Firmware version 2] Major confg changes
2025-01-09 [web app] Changes to support new configurations
2025-01-09 [Web app] Fix firmware version check
2025-01-16 Add docs for adding aprts
2025-01-16 Added more docs
2025-01-17 Added ability for UI to show Pre-release builds
2025-01-17 [Software] Fix issue for OTA update which PSP powered on.
2025-01-17 [CI] Default releases to prerelease
2025-02-02 [web app] Make web app handle RC releases when doing version check
2025-02-02 [Software] Changes button combo for cycle mappings. Added display button combo
2025-02-02 [web] Fix ci
2025-02-02 [Web] change to force build
2025-02-02 [Web] Another ci fix, maybe
2025-02-02 [web] my god just work
2025-02-04 [Software] changed analog to button sensitivity to handle diaganols,
2025-02-07 [software 2.2.0] Update readme to make releae official
2025-02-12 [Installer] Added initial settings page
2025-02-12 [software 2.3.0] Initial Settings confgurtion. Analog sticks need more work.
2025-02-12 [Software] Disable connections by default again
2025-02-12 [software] update release notes
2025-02-12 [software] fix led
2025-02-14 [installer] Remove diaganol from settings
2025-02-14 [software] Remove initial diaganol
2025-02-18 [Installer] Settings page -added shutdown timer, low battery
2025-02-18 [software] Final changes 2.8.3
2025-02-26 [installer] Update default warm boot delay to 5000
2025-02-26 [software] update warm boot delay
2025-02-26 [software] update release notes, again
2025-03-01 [Software] Added ability to configure mode button
2025-03-01 [Software] bump release notes version
2025-03-03 [installer] Update settngs to be percentage
2025-03-05 [Installer] Added button mode settings
2025-03-05 [Software] hange toggle power to just shutdown
2025-03-05 [Installer] Add firmware version warning
2025-03-06 [software] 2.3.1
2025-03-17 [Software] Fix mappings configuration via web app
2026-03-05 Update home page with Retro Protect and Retro Mods info
    Added information about Retro Protect's PlayStream product and updated the heading for Retro Mods Works.
